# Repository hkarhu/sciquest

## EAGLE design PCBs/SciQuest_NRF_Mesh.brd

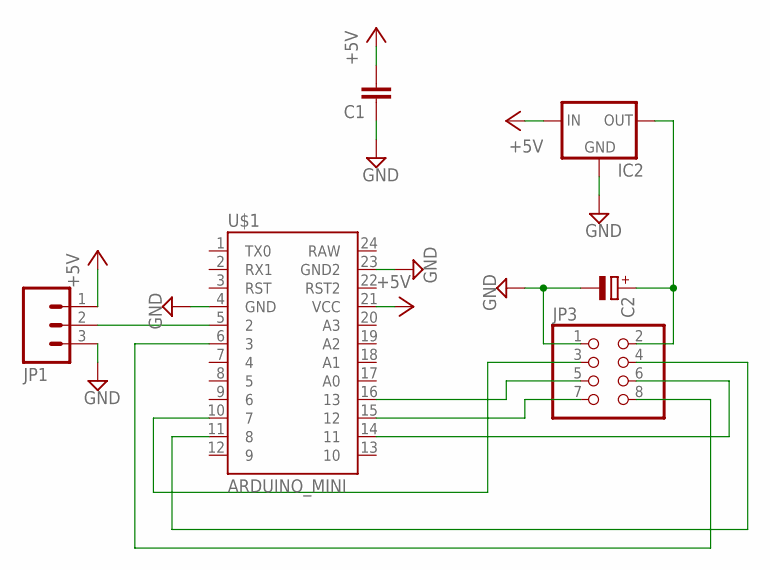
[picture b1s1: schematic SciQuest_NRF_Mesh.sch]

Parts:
C1: C-EUC0805K; C0805K
C2: CPOL-EUE2-4; E2-4
IC2: 78LXX
JP1: M03LONGPADS; 1X03_LONGPADS
JP3: PINHD-2X4; 2X04
U$1: ARDUINO_MINI

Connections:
+5V: C1.2, IC2.IN, JP1.1, U$1.21 (VCC)
GND: C1.1, C2.-, IC2.GND, JP1.3, JP3.1, U$1.4 (GND), U$1.23 (GND2)
unnamed: C2.+, IC2.OUT, JP3.2
unnamed: JP1.2, U$1.5 (2)
unnamed: JP3.3, U$1.10 (7)
unnamed: JP3.4, U$1.11 (8)
unnamed: JP3.5, U$1.16 (13)
unnamed: JP3.7, U$1.15 (12)
unnamed: JP3.6, U$1.14 (11)
unnamed: JP3.8, U$1.6 (3)

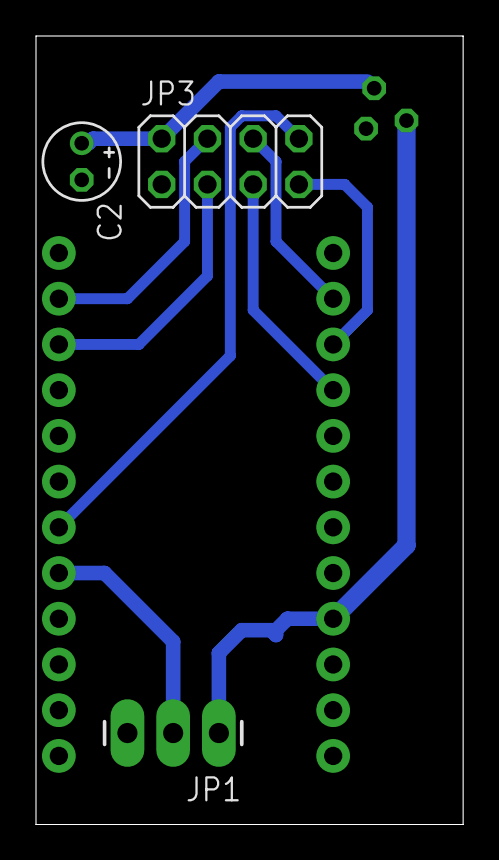
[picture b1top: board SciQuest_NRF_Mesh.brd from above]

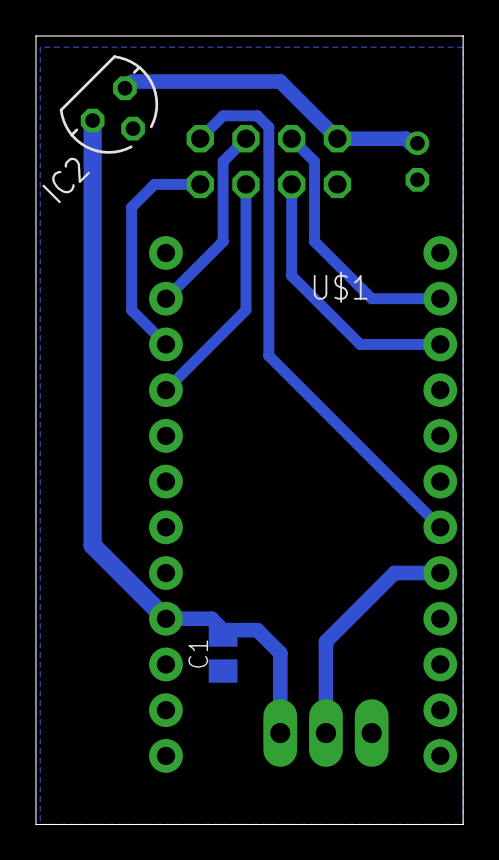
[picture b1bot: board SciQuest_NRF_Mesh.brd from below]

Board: 2 copper layers, 23.7 x 43.8 mm, 6 parts (3 on the bottom side), 10 nets.

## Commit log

2015-04-19 Casing modified
2015-04-20 NRF Tests
2015-04-20 Changes to the case
2015-04-21 Changes to chassis

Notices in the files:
parts and their libraries:
SparkFun: Licensing: CC v3.0 Share-Alike You are welcome to use this library for commercial purposes.
